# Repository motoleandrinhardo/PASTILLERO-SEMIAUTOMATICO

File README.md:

# PASTILLERO-SEMIAUTOMATICO
Este es un pastillero esmiautomatico que busca facilitar la tarea y control de la toma de madiamentos en personas mayores

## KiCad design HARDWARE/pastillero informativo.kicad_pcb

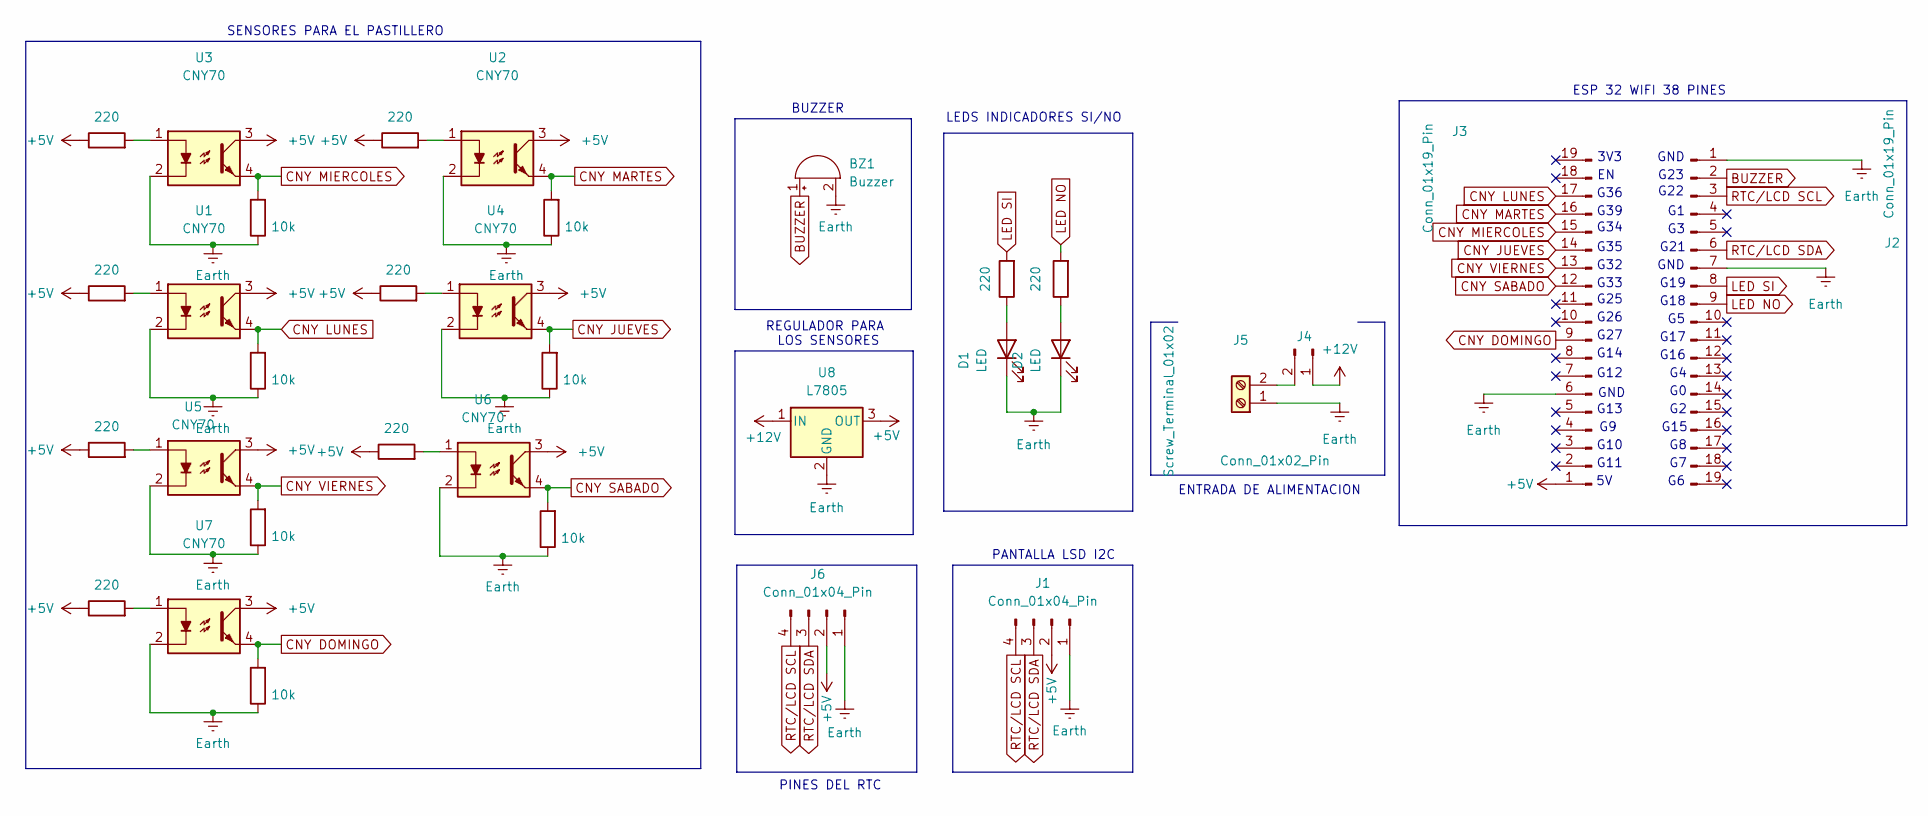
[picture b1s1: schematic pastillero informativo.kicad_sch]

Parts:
BZ1: Buzzer; Buzzer_TDK_PS1240P02BT_D12.2mm_H6.5mm
D1, D2: LED; LED_D3.0mm
J1, J6: Conn_01x04_Pin; PinHeader_1x04_P2.54mm_Vertical
J2, J3: Conn_01x19_Pin; PinHeader_1x19_P2.54mm_Vertical
J4: Conn_01x02_Pin; PinHeader_1x02_P2.54mm_Vertical
J5: Screw_Terminal_01x02; TerminalBlock_MaiXu_MX126-5.0-02P_1x02_P5.00mm
R1, R2, R12, R14, R16, R18, R20, R22, R23: 220; R_Axial_DIN0207_L6.3mm_D2.5mm_P7.62mm_Horizontal
R11, R13, R15, R17, R19, R21, R24: 10k; R_Axial_DIN0207_L6.3mm_D2.5mm_P7.62mm_Horizontal
U1, U2, U3, U4, U5, U6, U7: CNY70; PinHeader_1x04_P2.54mm_Vertical
U8: L7805; Converter_DCDC_TRACO_TSR2-24xxN_TSR2-24xxxN_THT

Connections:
+5V: J1.2, J3.1, J6.2, R12.1, R14.1, R16.1, R18.1, R20.1, R22.1, R23.1, U1.3, U2.3, U3.3, U4.3, U5.3, U6.3, U7.3, U8.3 (OUT)
+12V: J4.1, U8.1 (IN)
BUZZER: BZ1.1 (-), J2.2
CNY DOMINGO: J3.9, R17.2, U7.4
CNY JUEVES: J3.14, R13.2, U4.4
CNY LUNES: J3.17, R21.2, U1.4
CNY MARTES: J3.16, R11.2, U2.4
CNY MIERCOLES: J3.15, R24.2, U3.4
CNY SABADO: J3.12, R15.2, U6.4
CNY VIERNES: J3.13, R19.2, U5.4
Earth: BZ1.2 (+), D1.1 (K), D2.1 (K), J1.1, J2.1, J2.7, J3.6, J5.1, J6.1, R11.1, R13.1, R15.1, R17.1, R19.1, R21.1, R24.1, U1.2, U2.2, U3.2, U4.2, U5.2, U6.2, U7.2, U8.2 (GND)
LED NO: J2.9, R2.2
LED SI: J2.8, R1.2
unnamed: D1.2 (A), R1.1
unnamed: D2.2 (A), R2.1
unnamed: J4.2, J5.2
unnamed: R12.2, U3.1
unnamed: R14.2, U2.1
unnamed: R16.2, U1.1
unnamed: R18.2, U4.1
unnamed: R20.2, U5.1
unnamed: R22.2, U7.1
unnamed: R23.2, U6.1
RTC/LCD SCL: J1.4, J2.3, J6.4
RTC/LCD SDA: J1.3, J2.6, J6.3

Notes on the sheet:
G19
G11
ESP 32 WIFI 38 PINES
G26
GND
G34
G16
G36
ENTRADA DE ALIMENTACION
G13
3V3
G25
G22
G12
G15
G21
G10
G27
G23
PANTALLA LSD I2C
PINES DEL RTC
G39
G35
G32
SENSORES PARA EL PASTILLERO
REGULADOR PARA LOS SENSORES
G17
BUZZER
LEDS INDICADORES SI/NO
G14
G18
G33
GND

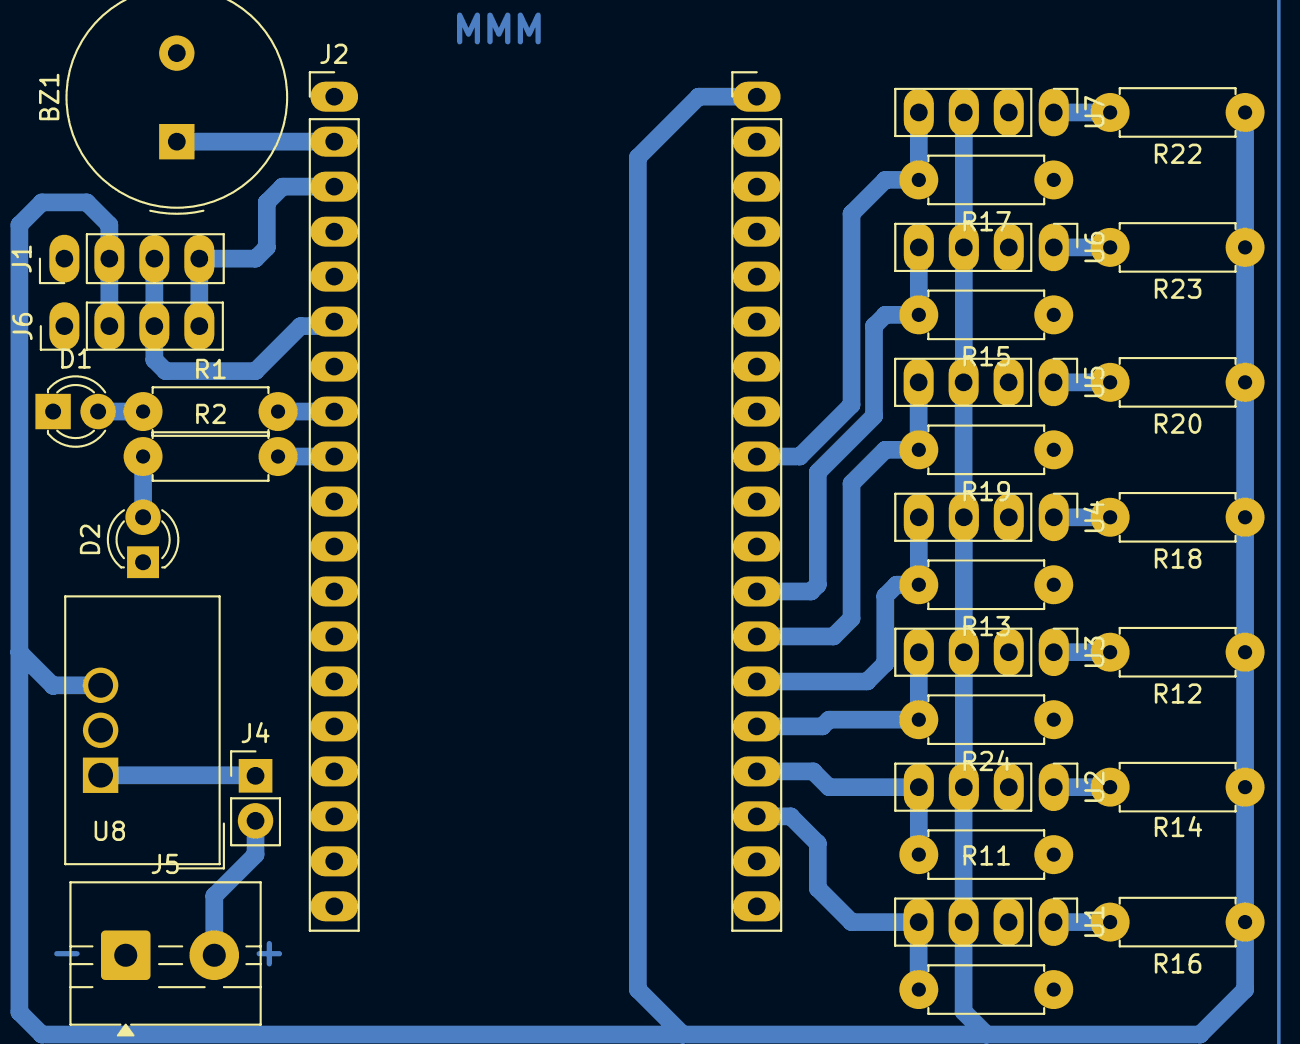
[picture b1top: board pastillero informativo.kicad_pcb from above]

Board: 2 copper layers, 33 parts (0 on the bottom side), 25 nets.
